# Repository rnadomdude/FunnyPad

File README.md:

# FunnyPad
Yet another basic 17 key numpad with kailh hotswap sockets designed for fun.  
Made with the [nice!nano v2](https://nicekeyboards.com/docs/nice-nano/), but compatible with any Pro Micro boards.  
My first PCB, please leave feedback. 

CAD model  
  
Exploded  
  
Wireframe  
  
PCB in kicad (2 layers)  
  
Schematic  

## Features
- Wired/Bluetooth with rechargeable battery (as many mAh as you want!!!)
- Kailh hotswap sockets!!!
- I spent my free time on this
- Screw on stabilizers
- ZMK compatibility

## Parts required
- nice!nano v2 x1
- kailh hotswap sockets x17
- 1N4148 through hole diodes x17
- M2*5mm screws x3
- M2*8mm screws x2
- M2*5mm Hexagonal threaded spacers x5 
- 301230 3.7v 110mAh battery x1
- 2U screw on stabs x3
- Socket for nice!nano x1
- Switches of your choice x17

## Assembly

## References
- Made with KiCad8 and FreeCad
- Software done and compiled with github actions using [ZMK](https://zmk.dev/)
- Schematic and PCB partly generated from https://kb.xyz.is/ used in conjunction with https://www.keyboard-layout-editor.com/#/
- Nice!nano footprint from https://github.com/ebastler/marbastlib

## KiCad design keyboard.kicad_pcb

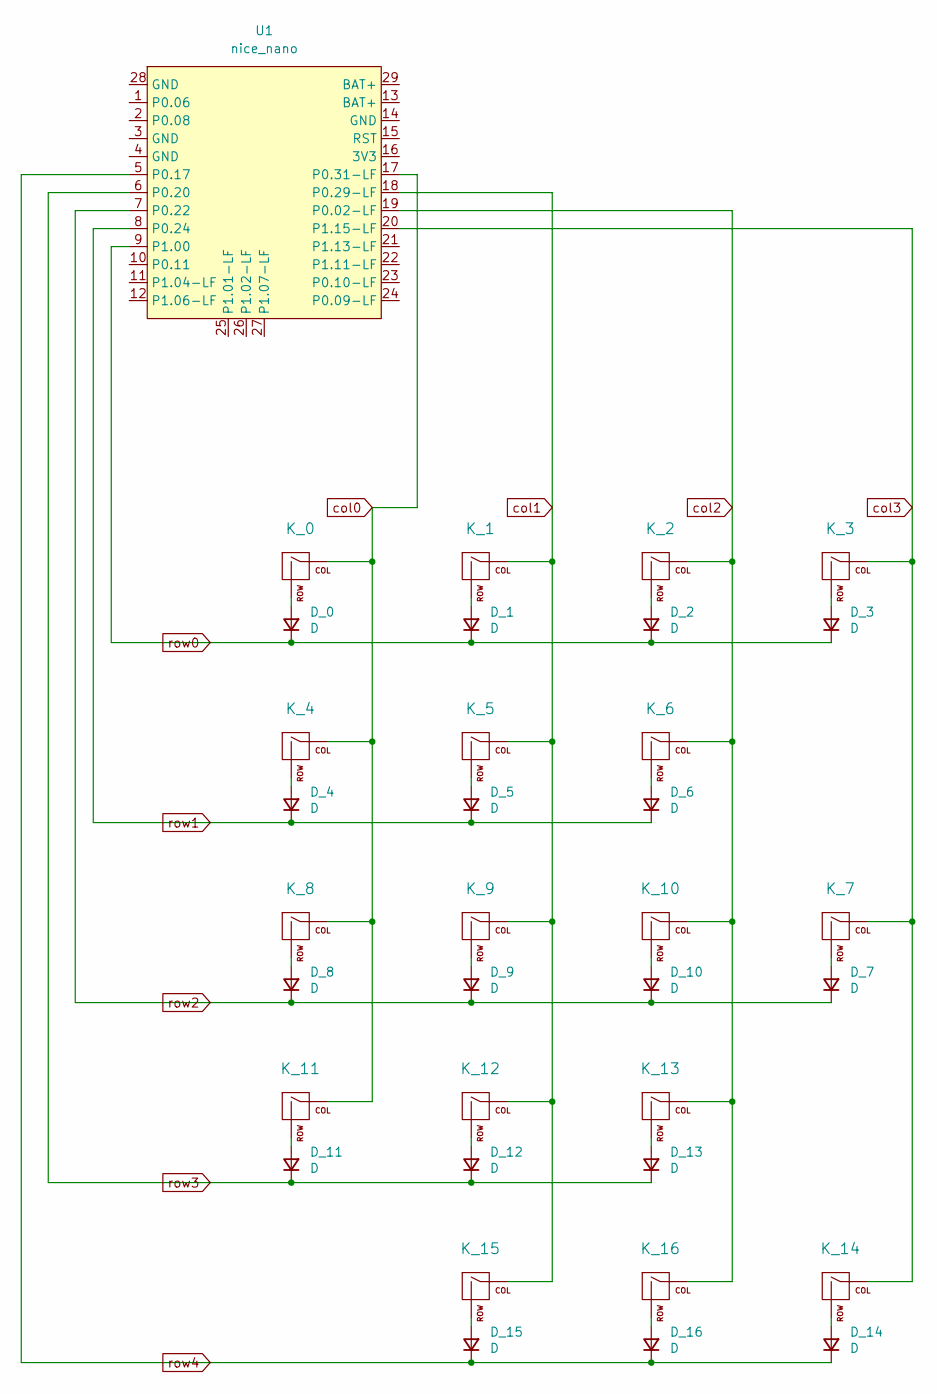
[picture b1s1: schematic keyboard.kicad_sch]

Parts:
D_0, D_1, D_2, D_3, D_4, D_5, D_6, D_7, D_8, D_9, D_10, D_11, D_12, D_13, D_14, D_15, D_16: D; D_SOD-123
K_0, K_1, K_2, K_3, K_4, K_5, K_6, K_7, K_8, K_9, K_10, K_11, K_12, K_13, K_14, K_16: KEYSW; MX-1U-NoLED
K_15: KEYSW; MX-2U-NoLED
U1: nice_nano; nice_nano_AH_USBup

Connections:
unnamed: D_0.2 (A), K_0.2 (ROW)
unnamed: D_1.2 (A), K_1.2 (ROW)
unnamed: D_2.2 (A), K_2.2 (ROW)
unnamed: D_3.2 (A), K_3.2 (ROW)
unnamed: D_4.2 (A), K_4.2 (ROW)
unnamed: D_5.2 (A), K_5.2 (ROW)
unnamed: D_6.2 (A), K_6.2 (ROW)
unnamed: D_7.2 (A), K_7.2 (ROW)
unnamed: D_8.2 (A), K_8.2 (ROW)
unnamed: D_9.2 (A), K_9.2 (ROW)
unnamed: D_10.2 (A), K_10.2 (ROW)
unnamed: D_11.2 (A), K_11.2 (ROW)
unnamed: D_12.2 (A), K_12.2 (ROW)
unnamed: D_13.2 (A), K_13.2 (ROW)
unnamed: D_14.2 (A), K_14.2 (ROW)
unnamed: D_15.2 (A), K_15.2 (ROW)
unnamed: D_16.2 (A), K_16.2 (ROW)
col0: K_0.1 (COL), K_4.1 (COL), K_8.1 (COL), K_11.1 (COL), U1.17 (P0.31-LF)
col1: K_1.1 (COL), K_5.1 (COL), K_9.1 (COL), K_12.1 (COL), K_15.1 (COL), U1.18 (P0.29-LF)
col2: K_2.1 (COL), K_6.1 (COL), K_10.1 (COL), K_13.1 (COL), K_16.1 (COL), U1.19 (P0.02-LF)
col3: K_3.1 (COL), K_7.1 (COL), K_14.1 (COL), U1.20 (P1.15-LF)
row0: D_0.1 (K), D_1.1 (K), D_2.1 (K), D_3.1 (K), U1.9 (P1.00)
row1: D_4.1 (K), D_5.1 (K), D_6.1 (K), U1.8 (P0.24)
row2: D_7.1 (K), D_8.1 (K), D_9.1 (K), D_10.1 (K), U1.7 (P0.22)
row3: D_11.1 (K), D_12.1 (K), D_13.1 (K), U1.6 (P0.20)
row4: D_14.1 (K), D_15.1 (K), D_16.1 (K), U1.5 (P0.17)

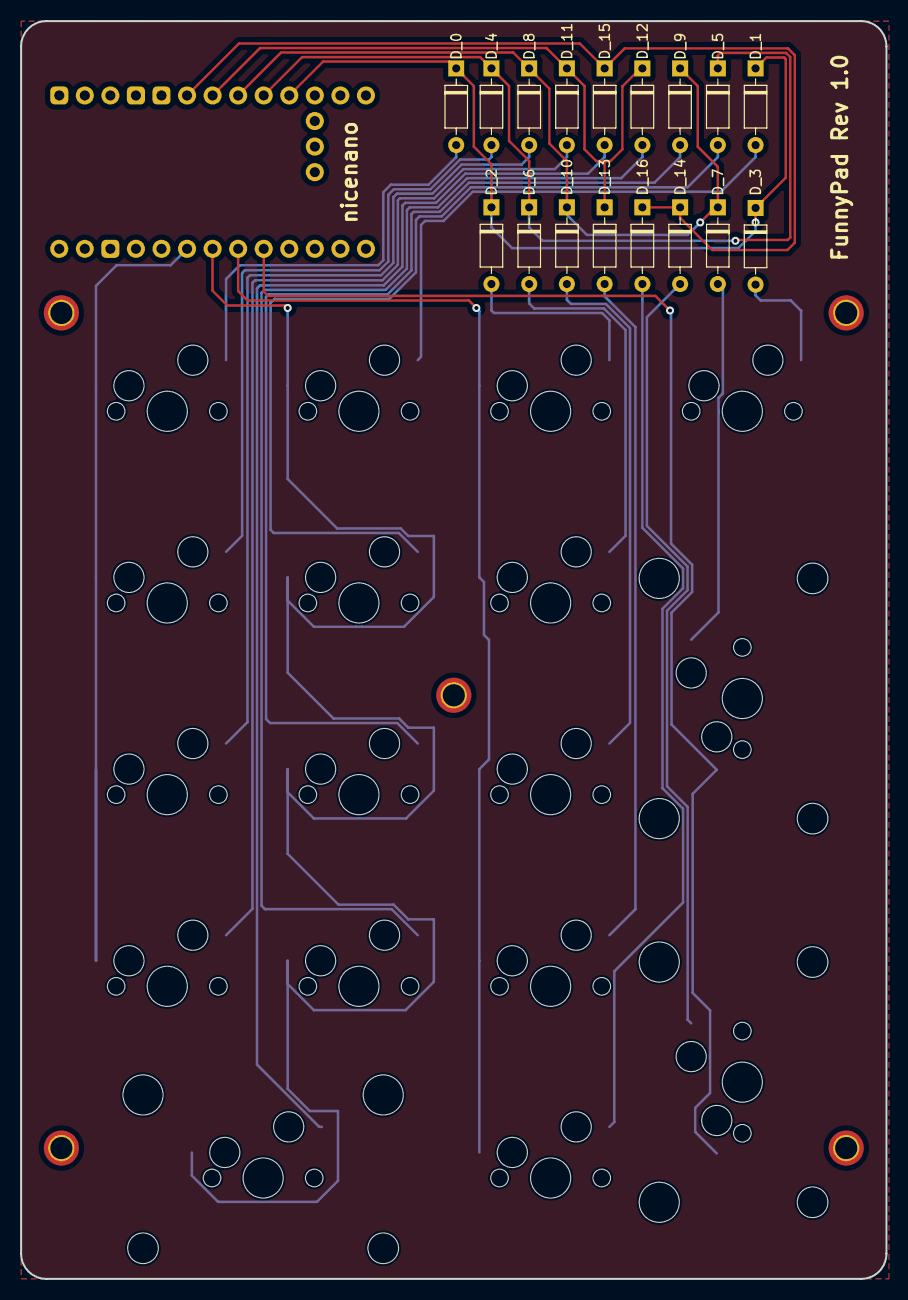
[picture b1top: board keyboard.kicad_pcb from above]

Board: 2 copper layers, 86.0 x 125.0 mm, 40 parts (1 on the bottom side), 26 nets.

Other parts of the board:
M2_1, M2_2, M2_3, M2_4, M2_5: MountingHole_2.2mm_M2_ISO7380_Pad_TopBottom

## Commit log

2024-12-06 keymap,conf,everything
2024-12-06 Update funnypad.overlay
    change from row2col to col2row
2024-12-06 Update funnypad.overlay
    i typo row 4 column 1 and 2
2024-12-06 change column 2 and 3 for row 4 funnypad.overlay
2024-12-06 added ZMK studio support
2024-12-20 Update funnypad.overlay because of trace issues
2024-12-20 Gerber and drill files for PCB
2024-12-20 KiCad files
2024-12-20 Measurement error fix
2024-12-20 Adjusted M2 screw positions and board size
2024-12-20 Adjusted M2 screw position and board size to 86*125mm
2024-12-21 Added STL files for keypad case
2024-12-22 Separated the foot and case for easier 3d printing
2024-12-28 Update readme and add images
2024-12-28 Added wireframe and exploded view
2024-12-28 oops
2025-03-02 Fixed foot fitting issue, usb cutout width, top edge fillet
2025-03-08 Update to restore 2nd layer
2025-03-10 removed matrix-transform
2025-03-10 added default matrix-transform in overlay
2025-03-10 removed chosen, matrix,transform
